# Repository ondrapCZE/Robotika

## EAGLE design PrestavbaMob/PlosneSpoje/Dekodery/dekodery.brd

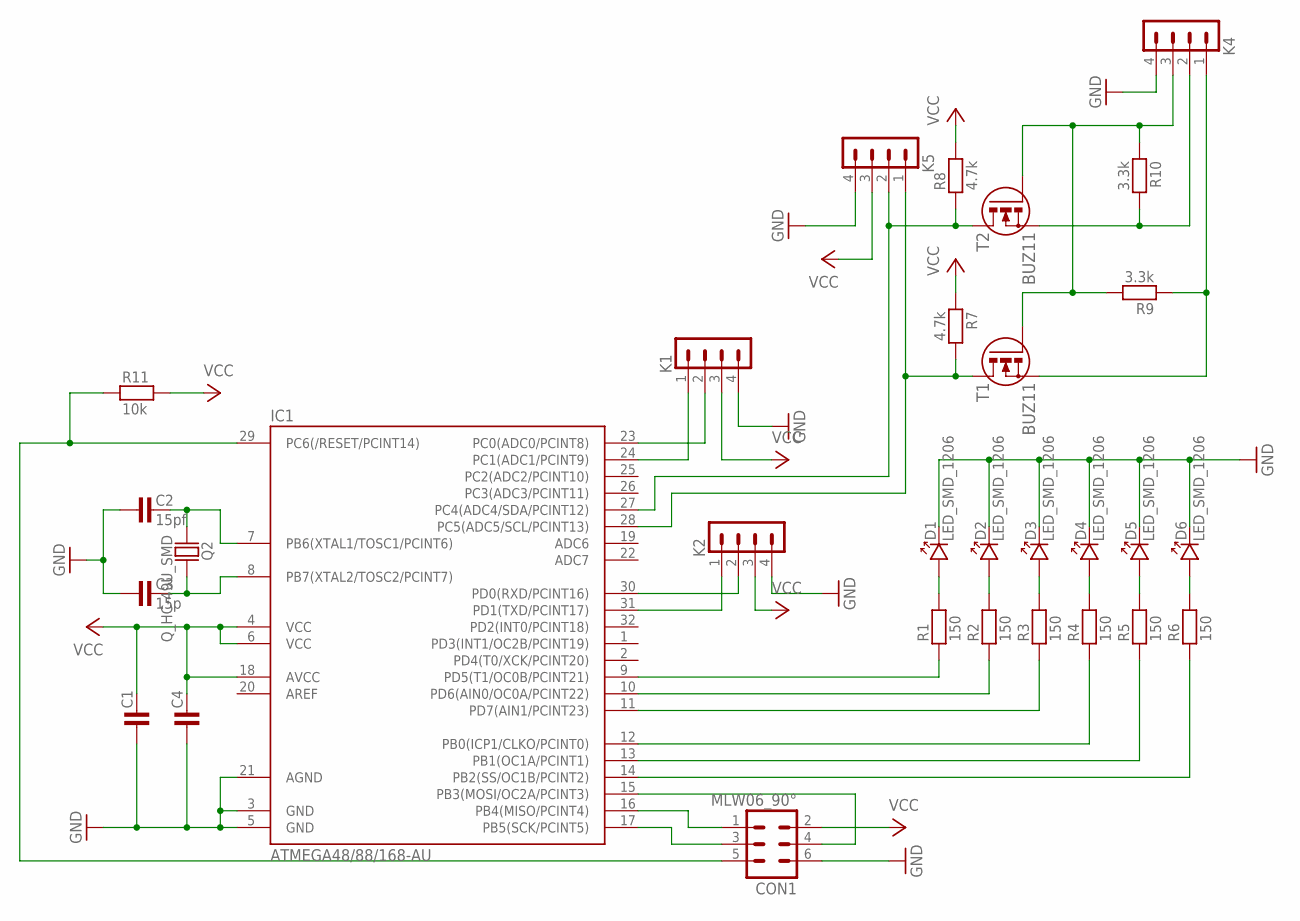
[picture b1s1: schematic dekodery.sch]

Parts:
C1, C4: C-KERAMIK_SMD_1206; 1206
C2: 15pf; 1206
C3: 15p; 1206
CON1: MLW06_90°; MLW06A
D1, D2, D3, D4, D5, D6: LED_SMD_1206; P1206
IC1: ATMEGA48/88/168-AU; TQFP32-08
K1, K2, K4, K5: PSH02-04W
Q2: Q_HC-49U_SMD; HC-49US
R1, R2, R3, R4, R5, R6: 150; 1206
R7, R8: 4.7k; 1206
R9, R10: 3.3k; 1206
R11: 10k; 1206
T1, T2: BUZ11; SOT23

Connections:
GND: C1.1, C2.1, C3.1, C4.1, CON1.6, D1.K, D2.K, D3.K, D4.K, D5.K, D6.K, IC1.3 (GND), IC1.5 (GND), IC1.21 (AGND), K1.4, K2.4, K4.4, K5.4
unnamed: IC1.30 (PD0(RXD/PCINT16)), K2.2
unnamed: IC1.31 (PD1(TXD/PCINT17)), K2.1
unnamed: IC1.23 (PC0(ADC0/PCINT8)), K1.2
unnamed: IC1.24 (PC1(ADC1/PCINT9)), K1.1
unnamed: IC1.28 (PC5(ADC5/SCL/PCINT13)), K5.1, R7.2, T1.3 (D)
unnamed: C3.2, IC1.8 (PB7(XTAL2/TOSC2/PCINT7)), Q2.2
unnamed: CON1.1, IC1.16 (PB4(MISO/PCINT4))
unnamed: CON1.3, IC1.17 (PB5(SCK/PCINT5))
unnamed: CON1.4, IC1.15 (PB3(MOSI/OC2A/PCINT3))
unnamed: IC1.9 (PD5(T1/OC0B/PCINT21)), R1.1
unnamed: IC1.10 (PD6(AIN0/OC0A/PCINT22)), R2.1
unnamed: IC1.11 (PD7(AIN1/PCINT23)), R3.1
unnamed: IC1.12 (PB0(ICP1/CLKO/PCINT0)), R4.1
unnamed: IC1.13 (PB1(OC1A/PCINT1)), R5.1
unnamed: IC1.14 (PB2(SS/OC1B/PCINT2)), R6.1
unnamed: D1.A, R1.2
unnamed: D6.A, R6.2
unnamed: D5.A, R5.2
unnamed: D4.A, R4.2
unnamed: D3.A, R3.2
unnamed: D2.A, R2.2
unnamed: C2.2, IC1.7 (PB6(XTAL1/TOSC1/PCINT6)), Q2.1
unnamed: IC1.27 (PC4(ADC4/SDA/PCINT12)), K5.2, R8.1, T2.3 (D)
unnamed: K4.3, R9.2, R10.1, T1.1 (G), T2.1 (G)
unnamed: K4.2, R10.2, T2.2 (S)
unnamed: K4.1, R9.1, T1.2 (S)
RST: CON1.5, IC1.29 (PC6(/RESET/PCINT14)), R11.1
VCC: C1.2, C4.2, CON1.2, IC1.4 (VCC), IC1.6 (VCC), IC1.18 (AVCC), K1.3, K2.3, K5.3, R7.1, R8.2, R11.2

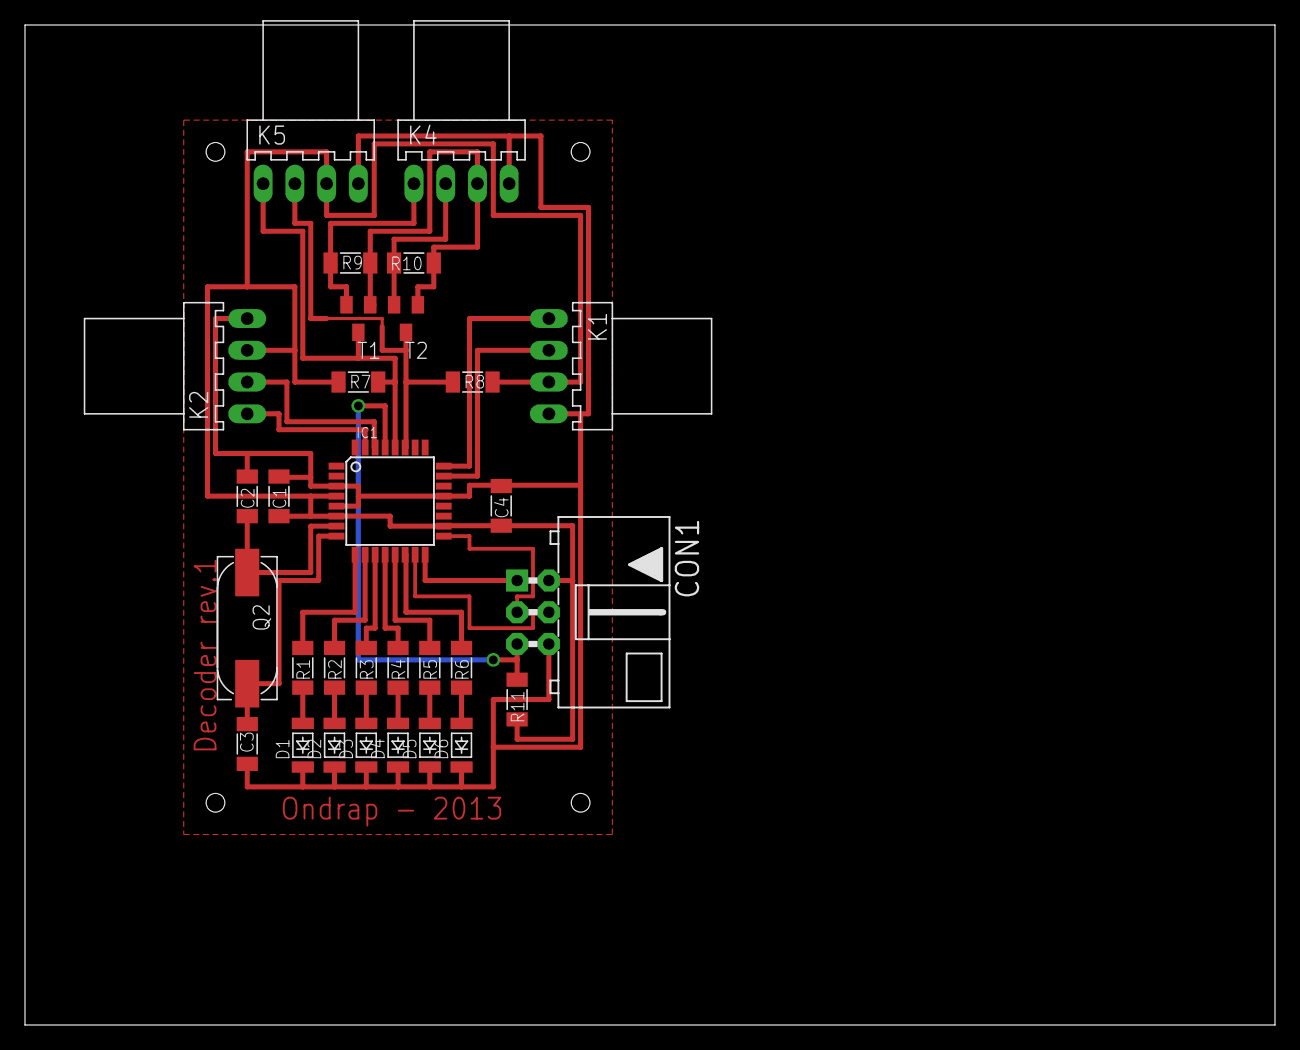
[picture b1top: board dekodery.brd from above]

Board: 2 copper layers, 100.0 x 80.0 mm, 30 parts (0 on the bottom side), 29 nets.

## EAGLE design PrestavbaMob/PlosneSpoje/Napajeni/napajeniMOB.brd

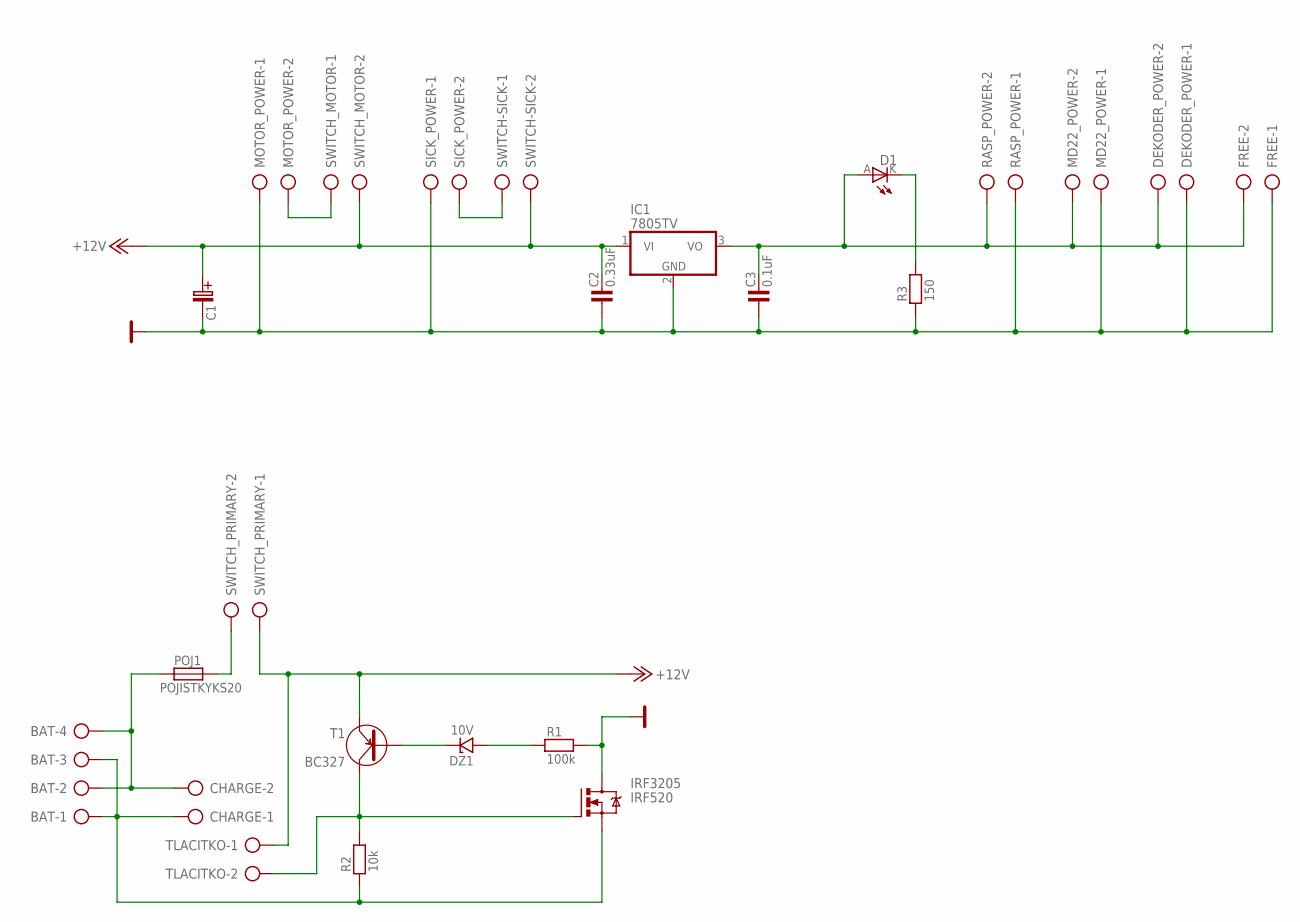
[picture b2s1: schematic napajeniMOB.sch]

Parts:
BAT: AK500/4
C1: C-ELEKTROLYT_7,5+; C-EL7,5+
C2: 0.33uF; C-5
C3: 0.1uF; C-5
CHARGE: AK500/2
D1: LEDLED5MM; LED5MM
DEKODER_POWER: AK500/2
DZ1: 10V; DO41
FREE: AK500/2
IC1: 7805TV; TO220V
IRF3205: IRF520; TO220BV
MD22_POWER: AK500/2
MOTOR_POWER: AK500/2
POJ1: POJISTKYKS20; POJ_KS20
R1: 100k; R-10
R2: 10k; R-10
R3: 150; R-10
RASP_POWER: AK500/2
SICK_POWER: AK500/2
SWITCH-SICK: AK500/2
SWITCH_MOTOR: AK500/2
SWITCH_PRIMARY: AK500/2
T1: BC327; TO-92
TLACITKO: AK500/2

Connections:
+12V: C1.C+ (C_EL+), C2.2, IC1.1 (VI), SWITCH-SICK.2, SWITCH_MOTOR.2, SWITCH_PRIMARY.1, T1.3 (E), TLACITKO.1
GND: C1.C- (C_EL-), C2.1, C3.1, DEKODER_POWER.1, FREE.1, IC1.2 (GND), IRF3205.D, MD22_POWER.1, MOTOR_POWER.1, R1.2, R3.1, RASP_POWER.1, SICK_POWER.1
GND_BATERIE: BAT.1, BAT.3, CHARGE.1, IRF3205.S, R2.1
unnamed: DZ1.A, R1.1
unnamed: BAT.2, BAT.4, CHARGE.2, POJ1.1
unnamed: DZ1.K, T1.2 (B)
unnamed: POJ1.2, SWITCH_PRIMARY.2
unnamed: IRF3205.G, R2.2, T1.1 (C), TLACITKO.2
unnamed: MOTOR_POWER.2, SWITCH_MOTOR.1
unnamed: SICK_POWER.2, SWITCH-SICK.1
unnamed: C3.2, D1.A, DEKODER_POWER.2, FREE.2, IC1.3 (VO), MD22_POWER.2, RASP_POWER.2
unnamed: D1.K (C), R3.2

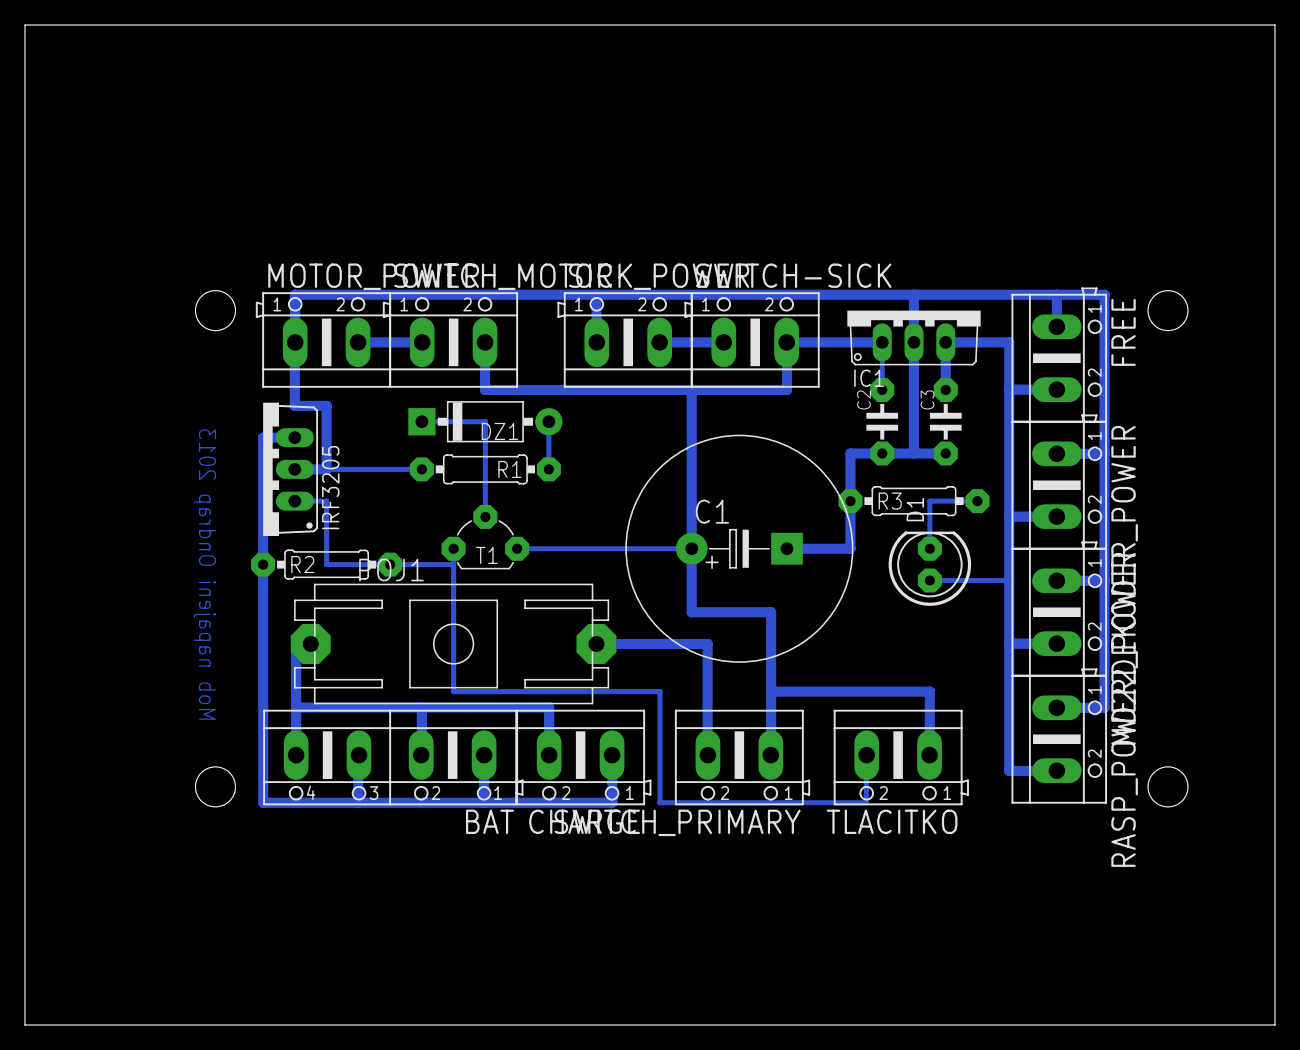
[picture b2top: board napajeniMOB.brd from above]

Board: 2 copper layers, 100.0 x 80.0 mm, 24 parts (0 on the bottom side), 12 nets.

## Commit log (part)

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2012-11-14 Pridany soubory s implementaci komunikace s gps ostarz pomoci seriove komunikace. Soubory otestovany pod win i linux.
2012-11-14 Pridan podpis. Pridana struktura pro GPS data.
2012-11-14 Pridana nova funkce getGPS, ktera vraci GPSData strukturu naplnenou aktualnimi gps daty.
2013-02-13 Pridany slozky obsahujici prvni verzi spodni desky pro napajeci a motorovou desku. V druhe slozce jsou navrhy plosnych spoju v soucasnosti pouze napajeci desky. Napajeci deska byla vyzkousena a fungu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
2013-02-19 Kod vycita enkodery bez problemu a funguje i komunikace po I2C. Jen neposila uplne spravne hodnoty enkoderu !!! Nefunguje nastavovani adresy v EEPROM.
2013-02-21 Pridany zaklady desky pro dekodery na moba. Pouze zapojeni enkoderu jeste se musi dodelat.
2013-03-14 Prvni verze desky pro dekodery.
2013-03-15 Pridan pull-up rezistor k resetu a zapojeni avcc.
2013-03-18 Upravena deska pro dekodery. Rozpracovano zapojeni soucastek a jejich propojeni na desce.
2013-03-26 Hotova verze desky rev.1 otestovana a napajena. Nepatrne upravy v kodu.
2013-03-28 Pridana nova podkladova deska na Moba jiz obsahuje diry na vsechny desky (MD22, napajeni, dekodery). Diry sedi a deska je v poradku.
2013-04-01 Prvni verze virtualni tridy zastupujici differencialni podvozek. Vytvorena trida pro implementaci virtualnich metod differencialniho podvozku.
2013-04-02 Komunikace funguje ale pouze pro prenos jednoho bytu!!! Musim se podivat kde je chyba v prenosu vice nez jednoho bytu.
2013-04-03 Dekoderu funguje citani stavu enkoderu. Chyba v komunikaci po i2c po urcite dobe uplne vymrzne v ziskavani informaci z bufferu.
2013-04-05 Dekodery software verze 1 vypada, ze funguje. Hurra.
2013-04-09 Castecna implementace tridy MobDifferencialChassisis vytvoren konstruktor, destruktor implementace virtualnich trid jeste se musi vytvorit zamky na cteni sdilenych dat. Vlakno jenz bude periodicky ci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
2013-04-09 Funkcni cteni stavu encoderu z i2c decoderu ve vlastnim vlaknu. Chybi pricitani aktualizace stavu encoderu. Musi se dodelat funkce a potom vlakno, ktere bude vykonavat akce s motory.
2013-04-12 Implementovan PIRegulator, ktery by jiz posila rychlost do kol podle pozadovane rychlosti. Nastavit konstanty PIRegulatoru a otestovat funkcnost.
2013-04-14 Pridana ochrana proti preteceni intu a maximalni rychlosti.
2013-04-16 Zacatek psani dokumentace. Vytvorena osnova a obrazky k osnove.
2013-04-17 Oprava chyby ohledne deadlocku pri vypadku komunikace s motory ci dekodery.
2013-04-17 Uprava kodu dekoderu aby interrupty pro vycitani tiku kol byli neblokujici. Po otestovani vypada, ze by mohli vhodne fungovat.
2013-04-22 Pridani kodu jenz vycita data z dalkoveho skeneru Tim310.
2013-04-22 Pridan soubor .gitignore pomoci ktereho lze ignorovat v repozitari urcite typy souboru.
2013-04-23 Funkcni verze s PI regulatorem. Chyby uz jen implementovat model pohybu pro upravu polohy robota v prostoru.
2013-04-24 Pridany soubory jenz budou implementovat zakladni pohyby podvozku jako jizdu rovne a otoceni o uhel.
2013-04-29 Pridan pdf soubor popisujici chovani SICK TIM310 a jeho zapojeni.
2013-05-07 Vytvorena dokumentace napajeci desky a dekoderove. V dokumentaci je popis zapojeni desek a konektoru na deskach.
2013-05-14 Provedena obnova dat z SD karty. Melo by fungovat jezdeni rovne a otaceni.
2013-05-15 Provedena kalibrace podvozku a robot jezdi rozumne jen se musi jeste upravit dojez robota na poslednich 10cm aby nezatacel. Vymazany debug hlasky.
2013-05-16 Pridano vypisovani z dalkoveho laseromeru s frekvenci 5hz.
2013-05-16 Vytvoren na tvrdo prujezd zakrutou a nasbirana data z prujezdu log1 - log5.
2013-05-23 Upravena dokumentace napajeci desky dle pripominek. Musi se jeste dodelat dokumentace u enkoderu.
2013-06-03 Pridan adresar s prevzatou implementaci MCL lokalizace z robota Umornik do Nemecka. Jiz pridana nova reprezentace mapy + zakladni zobrazeni + nacitani z logu.
2013-06-04 Uprava funkce pro vypocet pohybu ze dvou pozic.
2013-06-05 Dodelana funkce pro zobrazeni laseroveho skanu do mapy.
2013-06-06 Nahran log1.out na skutecnem hristi.
2013-06-06 Vytvoren bash script pro spusteni Bear rescue.
2013-06-06 Upraven zaznam dat ze sicka.
2013-06-06 Vytvoreno vraceni pruseciku se stenou pro stav. Musi se dodelat nejblizsi prusecik v dannem smeru.
2013-06-07 Odladena trida mapy. Jiz poskytuje spravne pruseciky jeste se podivat aby vracela spravne vzdalenosti.
2013-06-07 Fix bug: oprava vraceni nejblizsi vzdalnosti od sten uz vraci spravnou hodnotu double. + Spravne zobrazovani na mape.
2013-06-07 Trochu zprovoznena lokalizace fastSlam, ale moc tomu nedavam.
2013-06-07 Vytvoreno zakladni jezdeni bludiste s pomoci mcl.
2013-06-07 Vytvorena nabehova rampa pro pohyb.
2013-06-07 Posledni predzavodni upravy.
2013-06-07 Verze 0 s mcl lokalizaci. Dojede do obdelniku s medvidkem objede ctverec a vrati se domu.
2013-11-11 Add definition for motorDriver and move struct motorSpeed to this definition.
2013-11-11 Created and implemented class for MD22 motor driver without testing.
    TODO: Rewrite mobDifferencialChassis for using motorDriver class.
2013-11-11 Implemented part of Sabbertooth motor driver.
2013-11-11 Add partly implemented motorDriverSabertooth.
2013-11-13 First draft of mobDiff... with sabertooth motor driver.
2013-11-13 Tested mobDifferencialChassis with sabertooth motor driver and works. I seted PI parameters and wheel goes well.
2013-11-20 Code print debug message because comunication with decoder needs implement crc.
2013-11-20 Add CRC evalution to received data from decoder and when received damaged data discard this data and pull new one.
2013-11-21 Change some macros DEFINE to variable constant.
2013-11-21 Add empty files for encoders reader implementation.
2013-11-25 Start cleaning and prepearing all class for simple usage and parameters definition from config file.
2013-11-25 BUG Fix: Clear PIRegulator I value when someone call stop() function.
2013-11-25 Refactor motorDriver and all inherited class.
2013-11-26 Complete refactoring and cleaning in drivers class without documentation.
2013-11-26 Simplification of do while cyckle in getEncodersState for help of new function.
2013-11-26 Refactored basicDifferencialChassis header file for simpler understanding.
2013-11-29 Add interface definition for encoders reader.
2013-11-29 Add main file for testing.
2013-12-02 Add empty function moveCircle to the movement files.
2013-12-02 First version of moveCircle function.
2013-12-12 Empty file for stateMovement implementation.
2013-12-12 Bug fix: add longer wait for execution of clear display.
2013-12-12 Add output speed for movement go straight. TODO: Add negative speed when robot go backward.
2013-12-12 Fix header include because change the compiler to the g++-4.7
2013-12-18 Rewrite mutex and threads to c++11 standart with std::mutex and std::thread
2013-12-18 Complete implementation of tsqueue.
2013-12-18 Change name of stateMovement to checkpointMovement
2013-12-18 Bugfix: Fix correct use of lambda funtion in the tsqueue pop function.
2013-12-18 Add support for closing thread in checkpointMovementHermit.
2014-01-09 Implemented part of the checkpointMovementHermit and some operator in basic.h.
2014-01-09 Change type of mutex in mobDiff. Implemented part of the checkpointMovementHermit.
2014-01-09 Remove some bugs and yet testing and writing movement on hermit curves.
2014-01-09 Add outputVector computation and some debug printf.
2014-01-14 Add function for computation circle from state and point
2014-01-15 Working version: Hermit curve movement ;).
2014-01-21 Good working version.
2014-01-21 Add commet to the basicDiffChassis.
2014-01-22 Change parameters in hermit movements.
2014-01-22 Jerky motion on the hermit curve.
2014-02-19 Add signatures to the encoder files.
2014-02-19 Remove stop when is empty checkpoint queue.
2014-02-21 Add empty files for monte carlo localisation.
2014-03-19 Clear mcl and implement particle add.
2014-03-20 Create resample function.
2014-04-02 Add cmake for sabertooth.
2014-04-02 Add cmake for md22 driver.
2014-04-02 Add cmake for differencial chassis.
2014-04-02 Move files.
2014-04-04 Add new CMakes
2014-04-04 Move files in better location.
2014-04-10 Refactor: class private members, name of class
2014-04-10 Refactor private members and implemented slow stop.
2014-04-10 Bugfix: wrong comparision
2014-04-10 Fix: stop command.
2014-04-10 Use lock_guard.
2014-04-10 Debug messages.
2014-04-10 Rewrite: angle function
2014-04-10 Fix: robot can move only forward
2014-04-10 Rewrite getCircle now use intersection computing in homogenous coordinates.
2014-04-11 Add test if two lines is parallel.
2014-04-11 Fix: circle computing
2014-04-11 Fix: use std::abs instead of abs which is only for integer
2014-04-11 Comment all debug messages.
2014-04-17 Implemented move visitor.
2014-04-18 Add more mcl visitors.
2014-04-18 Patch: backward motion in hermit was replace with rotation and forward move
2014-04-24 Use dynamicly changing chassis params.
2014-05-07 Map: new definition and occupancy map
2014-05-10 OccupancyMap: implemented all method and add map updater
2014-05-14 MCL: reorder files in subdirectories
2014-05-14 Insert some logs from mob chassis
2014-05-21 Fix: correct typo
2014-05-21 OccupancyMap: rewrite public function so that all use world cordinates
2014-05-21 New logs from mob
2014-05-22 Add new measurement from desk
2014-05-28 Fix: errors in distance computation and particle resample
2014-05-28 Rename basic_robotic_fce on rob_fce
2014-05-28 Insert new measurement
2014-05-29 Partialy rewrited mclon Slam.
2014-06-05 Add new class
2014-06-05 Use Grid class instead of separately implemented grid.
2014-06-07 CostMap: partly implemented
2014-06-19 Add pause and resume to mob chassis checkpoint movements.
2014-06-19 Rewrite map distanceToNearestObstacle for returning interval value
2014-07-03 Fix weight error mcl.
2014-07-17 Add test on grid boundary and map.
2014-07-17 New log.
2014-07-17 Add fixed period to the hermit movement.
2014-07-31 Hermit: rewrite movement
2014-07-31 Debug prints
2014-07-31 Hermit: when angleDiff is bigger than 45degree robot only rotate
2014-07-31 Add new log
2014-08-07 New logs
2014-08-07 Clean source code.
2014-08-08 Create robot boundary around walls.
2014-09-10 CheckpointMovement: add new feathures as skipActualCheckpoint etc.
2014-09-10 CheckpointMovement: add callback function
2014-09-11 Working cost map, but little bit cpu consuming
2014-09-11 FrameConverter: convert between different frames
2014-09-11 Fix: test if callback_ was properly set
2014-09-23 FrameConverter: functional
2014-09-23 CostMap: some fixes
2014-09-23 Mob: change slow stop step speed
2014-09-24 Tsqueue: add methods for manipulating with end of the queue
2014-09-24 Position: add comparison operator
2014-09-24 FrameConverter: status method
2014-09-24 MCL: fix map update
2014-09-24 OccupancyUpdater: add max range defined by user
2014-10-02 Fix: addCheckpoint with vector
2014-10-02 Fix: pause -> pause_
2014-10-02 Fix: inverse condition
2014-10-02 Change logic about robot rotation in checkpoint movement
2014-10-02 Comment debug prints.
2014-10-02 Change default parameters.
2014-10-07 CostMap: add new public function
2014-10-12 Add virtual destructors in base classes.
2014-10-12 MotorDriverSabertooth: send stop to motors when destroid and delete test main
2014-10-12 Fix: compilation issues
2014-10-12 HermitMovement: fix pause and add checkpoint change in move to checkpoint function
2014-10-17 Movement: change all float to double
2014-10-17 Change float to double
2014-10-29 FrameConverter: fix translation and rotation between coordinate systems
2014-11-03 CheckpointMovement: fix end position in cycle
2014-11-03 CheckpointMovement: fix setting last position
2014-11-13 Documentation: add some of it
2014-11-13 Documentation: insert more public documentation for mob chassis.
2014-11-18 Add documentation.
2014-11-19 Fix: conversion between coordinates
2014-11-28 Change movement table.
2014-11-28 Insert wrapper arout boost file options
2014-11-28 Fix: remove printf

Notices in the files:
parts and their libraries:
Copyright (C) PaJa 2011
Copyright (C) PaJa 2001-2011
Copyright (C) Vlada 2004-2005
